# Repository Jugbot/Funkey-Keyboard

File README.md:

# Funkey-Keyboard ヽ(⌐■_■)ノ♪♬
### A piano with a built-in rhythm game! 
This was a project for New York University's prototyping design class (EG1003) for spring of 2018. The design won the Nick Russo Award and the I2E Award for Innovation.  

The idea behind this prototype was to make learning the piano easier by turning it into a sort of rhythm game. Other similar solutions exist out there such as [pianos that light up the next keys](https://www.smartpiano.com/) or tablet apps that record audio from an existing piano and use it as an input for a a [game-like learning tool](https://www.synthesiagame.com/). This prototype is slightly different in that it integrates 8 leds directly under every key. There is also the possibility of modularity due to the chainable input and display. 

Check out the [video demonstration](https://youtu.be/wlrPzlZg1Dw).

| Implemented | <ul><li>Automatic conversion of midi files to playable songs</li><li>Real time playback</li><li>Pseudo-random color change for differentiating notes</li></ul> |
| :--- | :--- |
| Unimplemented | <ul><li>Tempo must be input manually (bpm variable in code)</li><li>The circuit board for the buttons failed, so input recording and scoring was not able to be tested</li><li>As such the menu with scrolling text is not used in the last release and songs must be set beforehand in-code</li></ul> |

---
## Basic Specs
+ Raspberry Pi 3
+ Python 2

---
## Dependencies:
+ pyllist
+ python-midi
+ adafruit-gpio

---
## Hardware
I used the [ws2811 addressable rgb led string](http://a.co/irZiaNd) as a display.

For the inputs I decided to use [mcp23017 io port expander](https://www.adafruit.com/product/732) to demonstrate the possibility of modularity. 

Button Input/ LED Mount | Electrical Schematic 
----------------------- | -------------------- 
 |

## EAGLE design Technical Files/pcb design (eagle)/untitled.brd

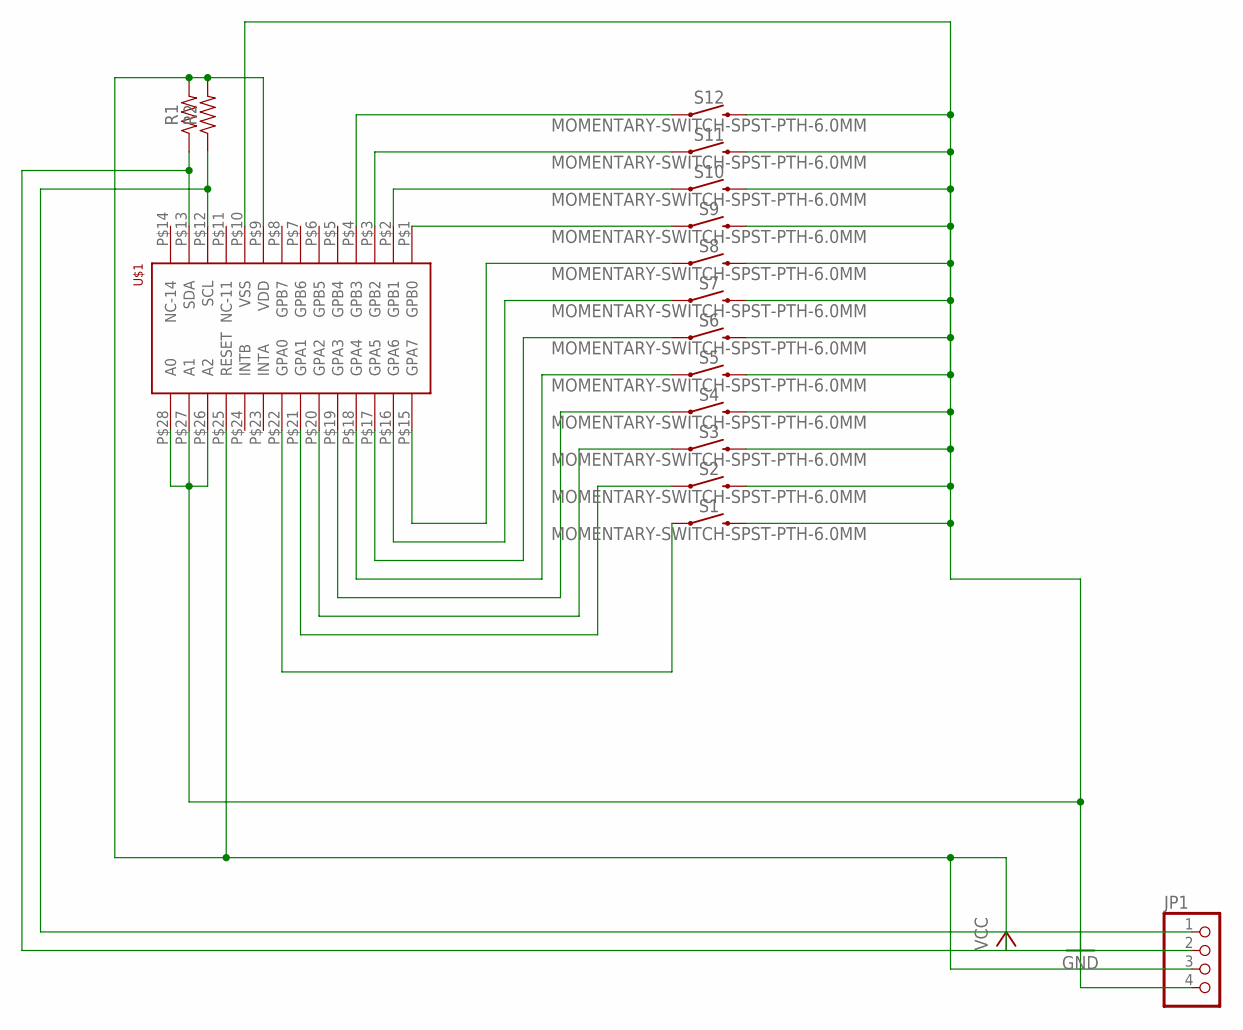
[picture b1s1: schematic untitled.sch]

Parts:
JP1: PINHD-1X4; 1X04
R1, R2: AXIAL-0.3
S1, S2, S3, S4, S5, S6, S7, S8, S9, S10, S11, S12: MOMENTARY-SWITCH-SPST-PTH-6.0MM; TACTILE_SWITCH_PTH_6.0MM
U$1: MCP23017-E/SP; DIP28

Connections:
GND: JP1.4, S1.3 (2), S2.3 (2), S3.3 (2), S4.3 (2), S5.3 (2), S6.3 (2), S7.3 (2), S8.3 (2), S9.3 (2), S10.3 (2), S11.3 (2), S12.3 (2), U$1.P$10 (VSS), U$1.P$26 (A2), U$1.P$27 (A1), U$1.P$28 (A0)
unnamed: S1.1, U$1.P$22 (GPA0)
unnamed: S2.1, U$1.P$21 (GPA1)
unnamed: S3.1, U$1.P$20 (GPA2)
unnamed: S4.1, U$1.P$19 (GPA3)
unnamed: S5.1, U$1.P$18 (GPA4)
unnamed: S6.1, U$1.P$17 (GPA5)
unnamed: S7.1, U$1.P$16 (GPA6)
unnamed: S8.1, U$1.P$15 (GPA7)
unnamed: S9.1, U$1.P$1 (GPB0)
unnamed: S10.1, U$1.P$2 (GPB1)
unnamed: S11.1, U$1.P$3 (GPB2)
unnamed: S12.1, U$1.P$4 (GPB3)
unnamed: JP1.2, R1.P$1 (1), U$1.P$13 (SDA)
unnamed: JP1.1, R2.P$1 (1), U$1.P$12 (SCL)
VCC: JP1.3, R1.P$2 (2), R2.P$2 (2), U$1.P$9 (VDD), U$1.P$25 (RESET)

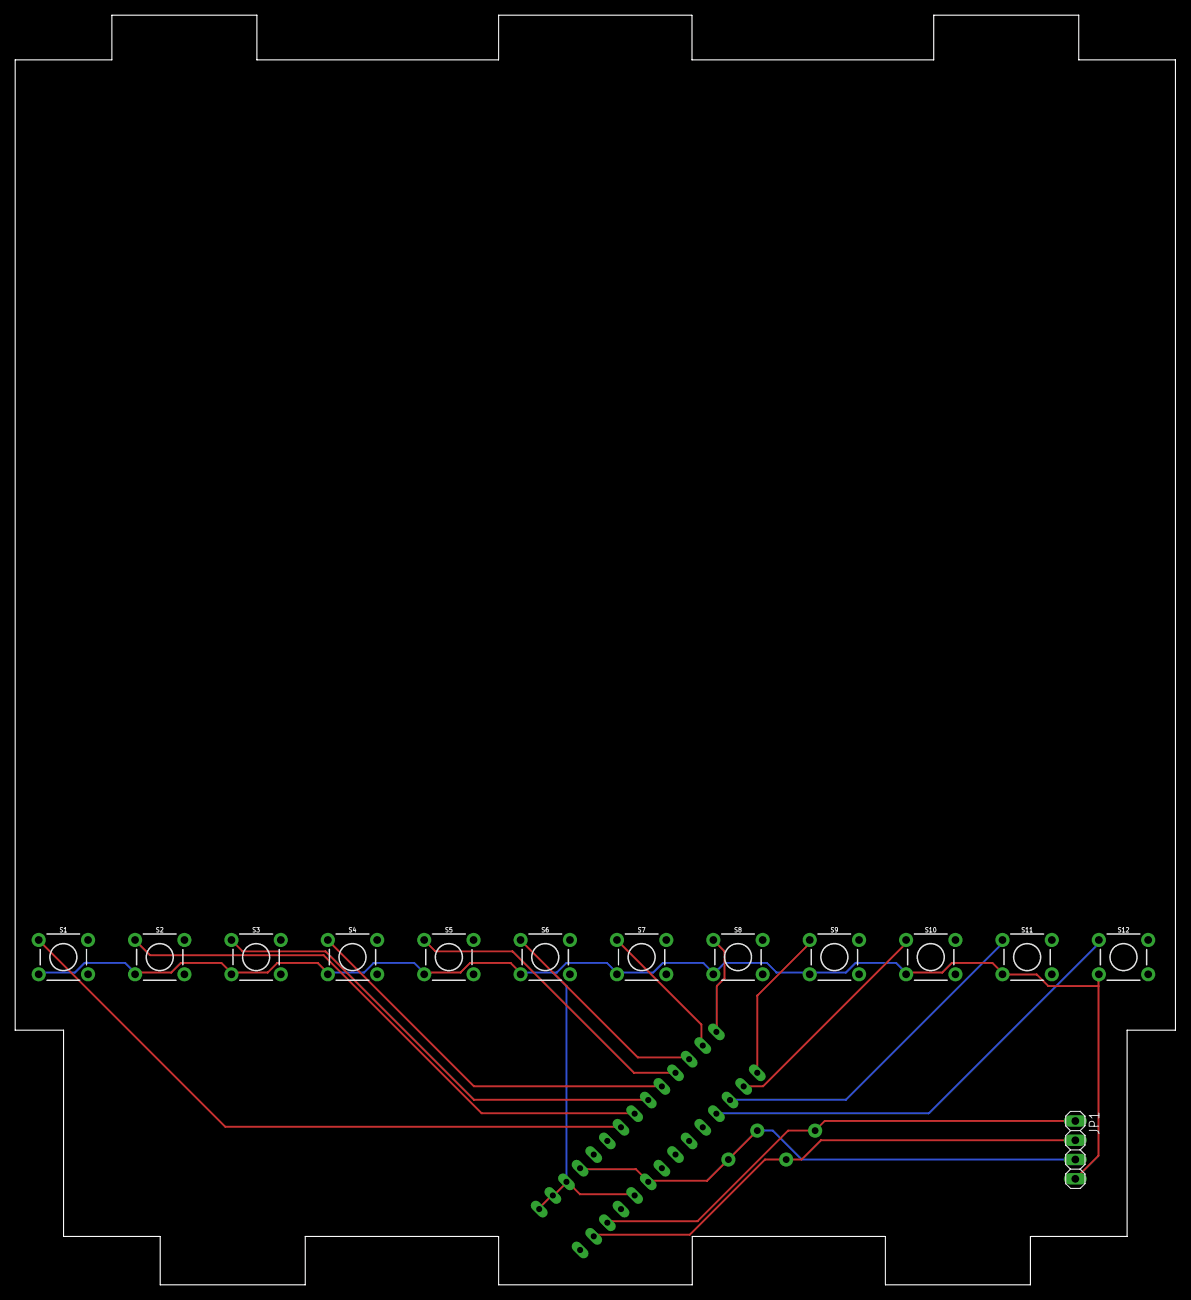
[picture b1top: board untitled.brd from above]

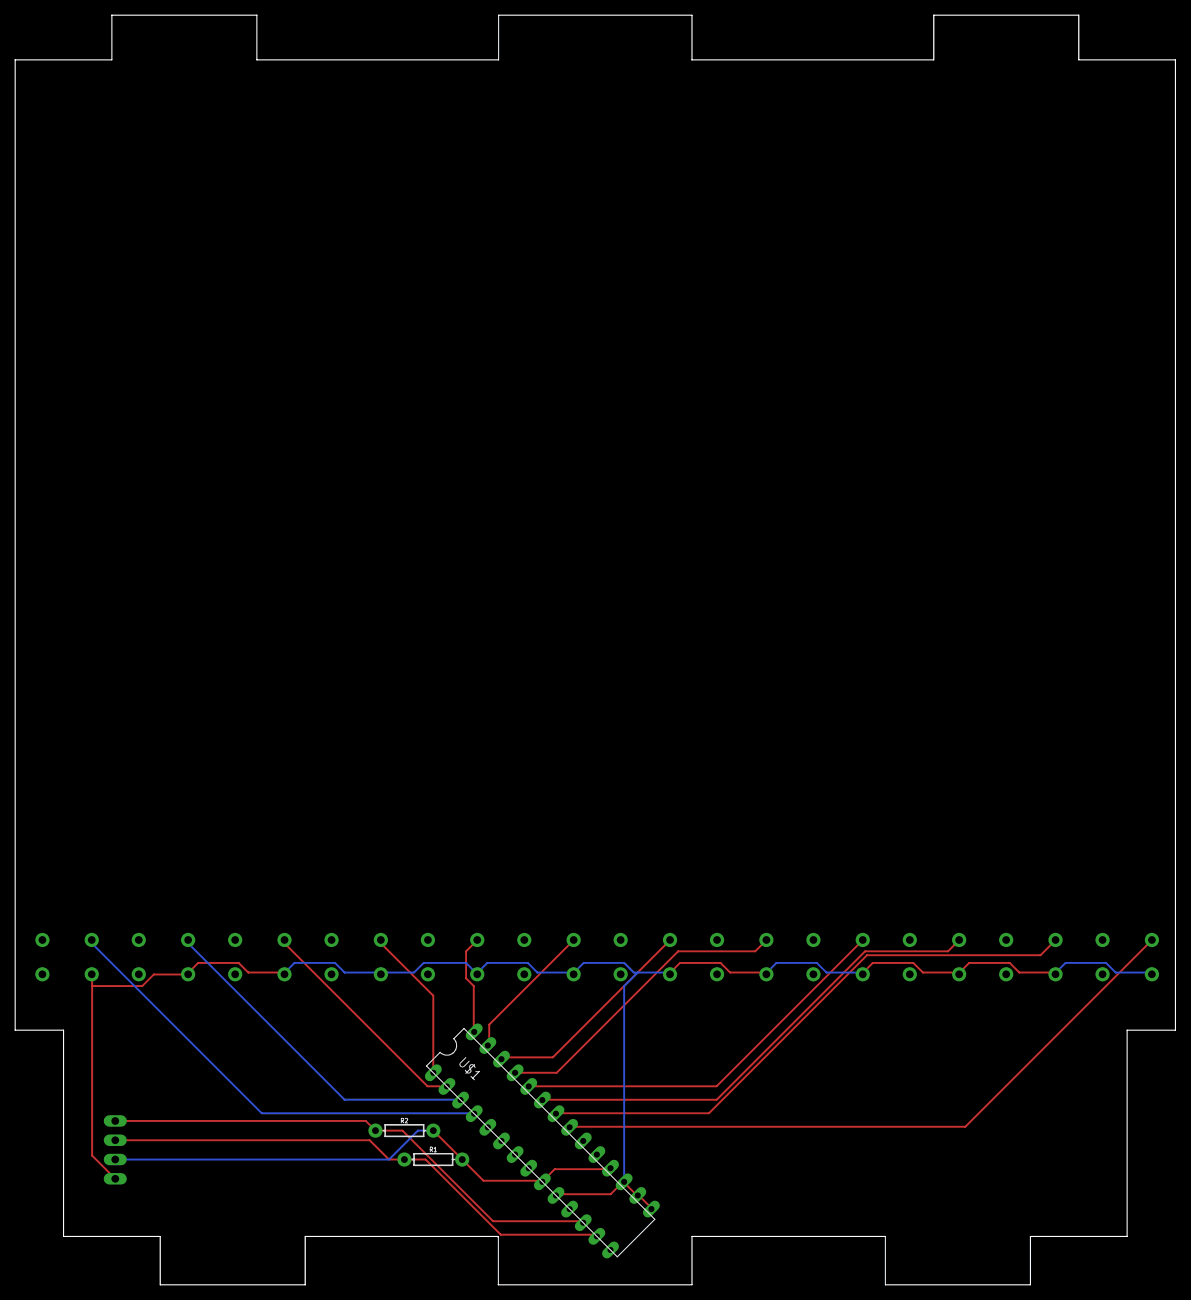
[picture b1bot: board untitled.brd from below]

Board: 2 copper layers, 152.9 x 167.3 mm, 16 parts (3 on the bottom side), 16 nets.

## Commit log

2018-03-24 added files
2018-03-24 Added terminal debug version
2018-03-24 readme update
2018-03-24 minor changes
2018-03-24 added M-W
2018-03-25 (broken)
2018-03-25 holy s*** it works
2018-03-25 stuff
2018-03-25 fixed N
2018-03-27 changes (nothing important)
2018-04-01 nothing important
2018-04-06 Button input and scoring
    Cleaned code and added multiprocessed button input register and scoring for when the song plays.
    Havent tested yet so garunteed not to work.
2018-04-19 Added keyboardInterrupt handling
2018-04-20 Made the menu pretty
2018-04-23 save
2018-05-16 cleaning up readme
2018-05-16 edit
2018-05-16 adding ignore list for IDE files
2018-05-16 fix ext
2018-05-16 remove IDE files
2018-05-16 Cleanup
2018-05-16 Image edit for style points
2018-05-16 Fixed svg page definition
2018-05-17 images for pcb

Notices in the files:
parts and their libraries:
SparkFun-Resistors: Licensing: Creative Commons ShareAlike 4.0 International - https://creativecommons.org/licenses/by-sa/4.0
